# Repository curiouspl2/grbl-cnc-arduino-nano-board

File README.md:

A PCB layout and schematic.

this is my fork with following features :

 * simple single sided board suitable for isolation routing
 * cheaper arduino mini instead of nano (no usb), can be used with my simplified single-sided arduino clone
 * additional A axis instead of spindle enable
 * ISP header (grbl cannot be programmed with bootloader anyway as it's too big)

TODO:
 * messy schematic and board, needs fixing
 * still using arduino nano header (unused pins just not connected) 
 * board is not really optimised
 * additional headers for tx/rx, fdti, additional arduino mini to support SD card, lcd and encoder

Made with Eagle PCB 8

##Requirements
* an arduino mini w atmega328 loaded with grbl http://github.com/grbl/grbl
* ISP programmer
* at least 1 Pololu A4988 Stepper motor driver
* power supply and motor ofcourse.

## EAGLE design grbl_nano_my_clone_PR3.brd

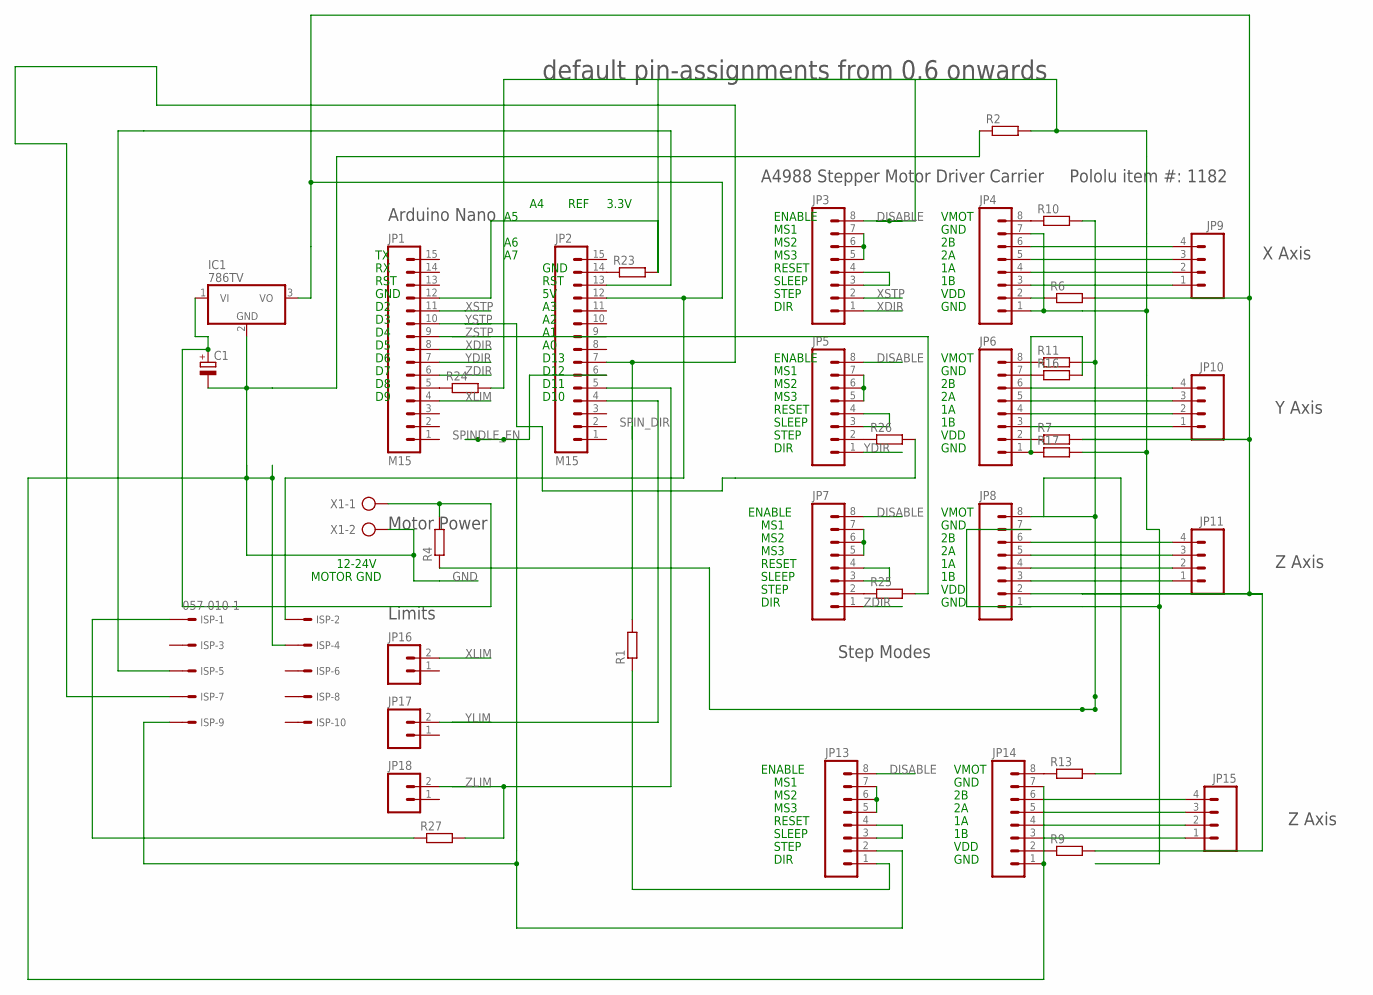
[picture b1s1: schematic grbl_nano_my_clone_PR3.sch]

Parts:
C1: CPOL-EUE3.5-8; E3,5-8
IC1: 786TV; TO220V
ISP: 057-010-1
JP1, JP2: M15; 1X15
JP3, JP4, JP5, JP6, JP7, JP8, JP13, JP14: M08LONGPADS; 1X08_LONGPADS
JP9, JP10, JP11, JP15: M04LONGPADS; 1X04_LONGPADS
JP16, JP17, JP18: M02LOCK_LONGPADS; 1X02_LOCK_LONGPADS
R1, R2, R6, R7, R9, R13, R23, R24, R25, R26, R27: R-EU_0207/15; 0207/15
R4, R16, R17: R-EU_0207/12; 0207/12
R10, R11: R-EU_0207/7; 0207/7
X1: AK300/2

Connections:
5V: IC1.3 (VO), ISP.2, JP2.12, JP8.2, R6.2, R7.2, R9.2
DISABLE: JP3.8, JP5.8, JP7.8, JP13.8, R24.2
GND: C1.-, IC1.2 (GND), ISP.4, JP14.1, JP14.7, R2.1, X1.2
GNDINT: JP1.12, JP4.1, JP4.7, JP8.1, JP8.7, R2.2, R17.2, R23.2
unnamed: JP5.3, JP5.4
unnamed: JP4.6, JP9.4
unnamed: JP4.5, JP9.3
unnamed: JP4.4, JP9.2
unnamed: JP4.3, JP9.1
unnamed: JP8.6, JP11.4
unnamed: JP8.5, JP11.3
unnamed: JP8.4, JP11.2
unnamed: JP8.3, JP11.1
unnamed: JP6.6, JP10.4
unnamed: JP6.5, JP10.3
unnamed: JP6.4, JP10.2
unnamed: JP6.3, JP10.1
unnamed: JP7.3, JP7.4
unnamed: JP3.3, JP3.4
unnamed: JP14.6, JP15.4
unnamed: JP14.5, JP15.3
unnamed: JP14.4, JP15.2
unnamed: JP14.3, JP15.1
unnamed: JP13.3, JP13.4
unnamed: JP13.1, R1.1
unnamed: ISP.5, JP2.13
unnamed: JP4.2, R6.1
unnamed: C1.+, IC1.1 (VI), R4.2, X1.1
unnamed: JP4.8, R10.1
unnamed: JP3.5, JP3.6, JP3.7
unnamed: JP5.2, R26.1
unnamed: JP14.2, R9.1
unnamed: JP6.8, R11.1
unnamed: JP14.8, R13.1
unnamed: JP6.7, R16.1
unnamed: JP6.1, R16.2, R17.1
unnamed: JP2.14, R23.1
unnamed: JP1.5, R24.1
unnamed: JP7.2, R25.1
unnamed: JP6.2, R7.1
unnamed: JP5.5, JP5.6, JP5.7
unnamed: ISP.1, R27.1
unnamed: JP7.5, JP7.6, JP7.7
unnamed: JP13.5, JP13.6, JP13.7
SPINDLE_EN: ISP.9, JP2.6, JP13.2
SPIN_DIR: ISP.7, JP2.7, R1.2
VMOT: JP8.8, R4.1, R10.2, R11.2, R13.2
XDIR: JP1.8, JP3.1
XLIM: JP1.4, JP16.2
XSTP: JP1.11, JP3.2
YDIR: JP1.7, JP5.1
YLIM: JP2.4, JP17.2
YSTP: JP1.10, R26.2
ZDIR: JP1.6, JP7.1
ZLIM: JP2.5, JP18.2, R27.2
ZSTP: JP1.9, R25.2

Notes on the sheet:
D10
GND
D11
D12
DIR
STEP
SLEEP
MS3
MS2
MS1
ENABLE
RESET
VDD
VMOT
default pin-assignments from 0.6 onwards
Step Modes
Arduino Nano
A4988 Stepper Motor Driver Carrier
Pololu item #: 1182
Motor Power
RST
REF
3.3V
D13
12-24V
MOTOR GND
Limits
X Axis
Y Axis
Z Axis

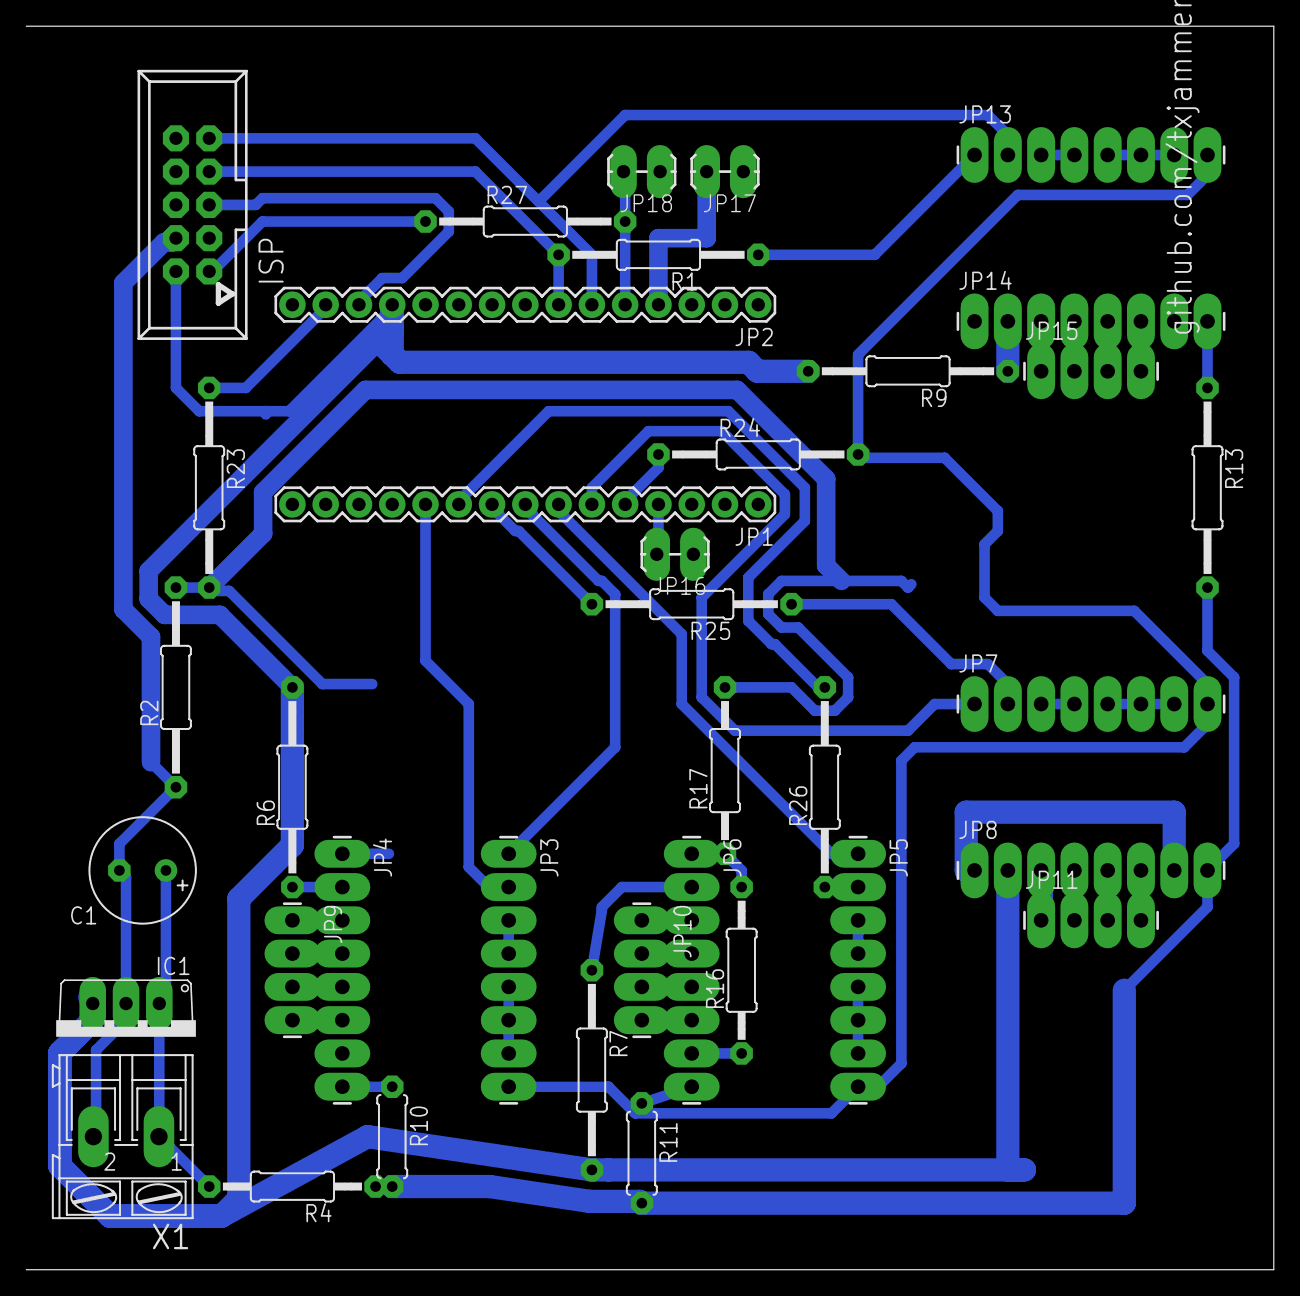
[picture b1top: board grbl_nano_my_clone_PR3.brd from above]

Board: 2 copper layers, 95.2 x 94.9 mm, 37 parts (0 on the bottom side), 56 nets.

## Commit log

2017-05-22 Add files via upload
    features of clone :
    -single sided board
    -cheaper arduino (mini) without usb
    -isp header (grbl is too big anyway)
    -A axis
    TODO:
